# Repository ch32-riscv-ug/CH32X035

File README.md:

# CH32X035

<!-- This file is generated from ch32-riscv-ug/ch32-device-data (index/ + evidence/ + pipeline/build/build_readme.py). Edit there, not here. -->

[Choose a part](#product-comparison) &middot; [Documents](#documents) &middot; [Pin maps](#pin-maps--alternate-functions) &middot; [Pin viewer](https://ch32-riscv-ug.github.io/ch32-device-data/pins.html?chip=CH32X033) &middot; [Errata](#errata) &middot; [Examples](#evt-examples) &middot; [Address map](#address-map)

## Quick start

Programming and debug: **2-wire SDI** (WCH-Link, `Serial Debug Interface`).

### Debug / serial defaults

Where these land **without writing a remap register**. SWD is live at reset; the UART pads are not -- the pin must still be put into alternate-function mode. See `route` in evidence/README.ja.md.

| Series | SWDIO | SWCLK | UART TX | UART RX |
|---|---|---|---|---|
| CH32X033 | PC18 | PC19 | PA2 (USART2); PB0 (USART4) | PA3 (USART2); PB1 (USART4) |
| CH32X035 | PC18 | PC19 | PB10 (USART1); PA2 (USART2) | PB11 (USART1); PA3 (USART2) |

### Datasheets and reference manual

- CH32X035DS0.PDF (datasheet): [English](https://ch32-riscv-ug.github.io/CH32X035/datasheet_en/CH32X035DS0.PDF) · [中文](https://ch32-riscv-ug.github.io/CH32X035/datasheet_zh/CH32X035DS0.PDF)
- CH32X035RM.PDF (reference manual): [English](https://ch32-riscv-ug.github.io/CH32X035/datasheet_en/CH32X035RM.PDF) · [中文](https://ch32-riscv-ug.github.io/CH32X035/datasheet_zh/CH32X035RM.PDF)

## Series

| Series | Core | ISA | Flash | SRAM | Main clock | VDD | Packages | Products | Official |
|---|---|---|---|---|---|---|---|---|---|
| **CH32X033** | QingKe V4C | RV32IMAC | 62K | 20K | 48 MHz\* | 2.0-5.5V | TSSOP20 | 1 | [en](https://www.wch-ic.com/products/CH32X033.html) / [zh](https://www.wch.cn/products/CH32X033.html) |
| **CH32X035** | QingKe V4C | RV32IMAC | 62K | 20K | 48 MHz\* | 2.0-5.5V | LQFP48,LQFP64M,QFN12,QFN20,QFN28,QSOP28,TSSOP20 | 7 | [en](https://www.wch-ic.com/products/CH32X035.html) / [zh](https://www.wch.cn/products/CH32X035.html) |

\* the datasheet states no nominal system main frequency for this series, so the figure is the electrical maximum (HCLK) from the characteristics table -- a limit, not a rating.

## Product comparison

### CH32X035 product comparison

Only the 7 rows that differ between these 7 products; the other 10 are the same for all of them.

| | [CH32X035&#8203;C8T6](https://ch32-riscv-ug.github.io/ch32-device-data/pins.html?chip=CH32X035C8T6)&#8203;(LQFP48) | [CH32X035&#8203;D8U6](https://ch32-riscv-ug.github.io/ch32-device-data/pins.html?chip=CH32X035D8U6)&#8203;(QFN12) | [CH32X035&#8203;F7P6](https://ch32-riscv-ug.github.io/ch32-device-data/pins.html?chip=CH32X035F7P6)&#8203;(TSSOP20) | [CH32X035&#8203;F8U6](https://ch32-riscv-ug.github.io/ch32-device-data/pins.html?chip=CH32X035F8U6)&#8203;(QFN20) | [CH32X035&#8203;G8R6](https://ch32-riscv-ug.github.io/ch32-device-data/pins.html?chip=CH32X035G8R6)&#8203;(QSOP28) | [CH32X035&#8203;G8U6](https://ch32-riscv-ug.github.io/ch32-device-data/pins.html?chip=CH32X035G8U6)&#8203;(QFN28) | [CH32X035&#8203;R8T6](https://ch32-riscv-ug.github.io/ch32-device-data/pins.html?chip=CH32X035R8T6)&#8203;(LQFP64M) |
|---|---|---|---|---|---|---|---|
| **GPIO** | 46 | 11 | 18 | 19 | 26 | 27 | 60 |
| Serial port | 4 | 3 | 3 | 3 | 4 | 4 | 4 |
| PDUSB USB Host | √ | - | - | - | √ | √ | √ |
| ADC | 10+1 | 5+1 | 11+1 | 10+1 | 11+1 | 12+1 | 14+1 |
| OPA | 2 | 1 | 1 | 2 | 2 | 2 | 2 |
| CMP | 3 | - | 1 | - | 3 | 1 | 3 |
| Capacitive Touchkey | 10 | 5 | 11 | 10 | 11 | 12 | 14 |

<details><summary>All 17 rows</summary>

| | [CH32X035&#8203;C8T6](https://ch32-riscv-ug.github.io/ch32-device-data/pins.html?chip=CH32X035C8T6)&#8203;(LQFP48) | [CH32X035&#8203;D8U6](https://ch32-riscv-ug.github.io/ch32-device-data/pins.html?chip=CH32X035D8U6)&#8203;(QFN12) | [CH32X035&#8203;F7P6](https://ch32-riscv-ug.github.io/ch32-device-data/pins.html?chip=CH32X035F7P6)&#8203;(TSSOP20) | [CH32X035&#8203;F8U6](https://ch32-riscv-ug.github.io/ch32-device-data/pins.html?chip=CH32X035F8U6)&#8203;(QFN20) | [CH32X035&#8203;G8R6](https://ch32-riscv-ug.github.io/ch32-device-data/pins.html?chip=CH32X035G8R6)&#8203;(QSOP28) | [CH32X035&#8203;G8U6](https://ch32-riscv-ug.github.io/ch32-device-data/pins.html?chip=CH32X035G8U6)&#8203;(QFN28) | [CH32X035&#8203;R8T6](https://ch32-riscv-ug.github.io/ch32-device-data/pins.html?chip=CH32X035R8T6)&#8203;(LQFP64M) |
|---|---|---|---|---|---|---|---|
| **Flash** | 62K | 62K | 62K | 62K | 62K | 62K | 62K |
| **SRAM** | 20K | 20K | 20K | 20K | 20K | 20K | 20K |
| **GPIO** | 46 | 11 | 18 | 19 | 26 | 27 | 60 |
| **Temperature** | -40..85C | -40..85C | -40..85C | -40..85C | -40..85C | -40..85C | -40..85C |
| Advanced-control timer | 2 | 2 | 2 | 2 | 2 | 2 | 2 |
| General-purpose timer | 1 | 1 | 1 | 1 | 1 | 1 | 1 |
| Serial port | 4 | 3 | 3 | 3 | 4 | 4 | 4 |
| Watchdog | 2 | 2 | 2 | 2 | 2 | 2 | 2 |
| PDUSB USB Host | √ | - | - | - | √ | √ | √ |
| USB Device | √ | √ | √ | √ | √ | √ | √ |
| Type-C Source Sink DRP | √ | √ | √ | √ | √ | √ | √ |
| ADC | 10+1 | 5+1 | 11+1 | 10+1 | 11+1 | 12+1 | 14+1 |
| OPA | 2 | 1 | 1 | 2 | 2 | 2 | 2 |
| CMP | 3 | - | 1 | - | 3 | 1 | 3 |
| Capacitive Touchkey | 10 | 5 | 11 | 10 | 11 | 12 | 14 |
| SPI | √ | √ | √ | √ | √ | √ | √ |
| PIOC 1-wire interface | √ | √ | √ | √ | √ | √ | √ |

</details>

## Block diagrams

### CH32X033

<details><summary>Internal block diagram (datasheet)</summary>

</details>

### CH32X035

System block diagram from the [WCH product page](https://www.wch-ic.com/products/CH32X035.html).

<details><summary>Internal block diagram (datasheet)</summary>

</details>

## Documents

| Document | Kind | English | 中文 |
|---|---|---|---|
| CH32X035DS0.PDF | datasheet | [page](https://www.wch-ic.com/downloads/CH32X035DS0_PDF.html) [mirror](https://ch32-riscv-ug.github.io/CH32X035/datasheet_en/CH32X035DS0.PDF) v2.3 | [page](https://www.wch.cn/downloads/CH32X035DS0_PDF.html) [mirror](https://ch32-riscv-ug.github.io/CH32X035/datasheet_zh/CH32X035DS0.PDF) v2.3 |
| CH32X035RM.PDF | reference-manual | [page](https://www.wch-ic.com/downloads/CH32X035RM_PDF.html) [mirror](https://ch32-riscv-ug.github.io/CH32X035/datasheet_en/CH32X035RM.PDF) v1.9 | [page](https://www.wch.cn/downloads/CH32X035RM_PDF.html) [mirror](https://ch32-riscv-ug.github.io/CH32X035/datasheet_zh/CH32X035RM.PDF) v2.0 |
| CH32X035EVT.ZIP | evt | - | [page](https://www.wch.cn/downloads/CH32X035EVT_ZIP.html) [mirror](https://github.com/ch32-riscv-ug/CH32X035/tree/main/EVT) v2.31 |
| CHRISC8B.PDF | core-manual | [mirror](https://ch32-riscv-ug.github.io/CH32X035/EVT/EXAM/PIOC/Tool_Manual/Manual/CHRISC8B-EN.pdf) v2B | [mirror](https://ch32-riscv-ug.github.io/CH32X035/EVT/EXAM/PIOC/Tool_Manual/Manual/CHRISC8B.PDF) v2B |
| PIOC.PDF | core-manual | [mirror](https://ch32-riscv-ug.github.io/CH32X035/EVT/EXAM/PIOC/Tool_Manual/Manual/PIOC-EN.pdf) v1.0 | [mirror](https://ch32-riscv-ug.github.io/CH32X035/EVT/EXAM/PIOC/Tool_Manual/Manual/PIOC.PDF) v1.1 |

### Evaluation boards

- board-manual:en: [CH32X035 Evaluation Board Reference-EN.pdf](https://ch32-riscv-ug.github.io/CH32X035/EVT/PUB/CH32X035%20Evaluation%20Board%20Reference-EN.pdf)
- board-manual:zh: [CH32X035评估板说明书.pdf](https://ch32-riscv-ug.github.io/CH32X035/EVT/PUB/CH32X035%E8%AF%84%E4%BC%B0%E6%9D%BF%E8%AF%B4%E6%98%8E%E4%B9%A6.pdf)
- schematic-pdf: [CH32X035SCH.pdf](https://ch32-riscv-ug.github.io/CH32X035/EVT/PUB/CH32X035SCH.pdf)

7 board schematics under `EVT/PUB/SCHPCB/`: `CH32X033F8P-R0`, `CH32X035C8T-R0`, `CH32X035F7P-R0`, `CH32X035F8U-R0`, `CH32X035G8R-R0`, `CH32X035G8U-R0`, `CH32X035USBPD-CH211`

## Packages & pinout drawings

Pinout drawings are in the datasheet (chapter *Pinouts*); each link opens at the page that carries the drawing:

| Package | Products | Datasheet | Outline |
|---|---|---|---|
| TSSOP20 | CH32X033F8P6 | [en](https://ch32-riscv-ug.github.io/CH32X035/datasheet_en/CH32X035DS0.PDF#page=16) / [zh](https://ch32-riscv-ug.github.io/CH32X035/datasheet_zh/CH32X035DS0.PDF#page=15) | [drawing](https://raw.githubusercontent.com/ch32-riscv-ug/WCH-common/main/image/package_TSSOP20.png) |
| LQFP48 | CH32X035C8T6 | [en](https://ch32-riscv-ug.github.io/CH32X035/datasheet_en/CH32X035DS0.PDF#page=13) / [zh](https://ch32-riscv-ug.github.io/CH32X035/datasheet_zh/CH32X035DS0.PDF#page=12) | [drawing](https://raw.githubusercontent.com/ch32-riscv-ug/WCH-common/main/image/package_LQFP48.png) |
| QFN12 | CH32X035D8U6 | [en](https://ch32-riscv-ug.github.io/CH32X035/datasheet_en/CH32X035DS0.PDF#page=15) / [zh](https://ch32-riscv-ug.github.io/CH32X035/datasheet_zh/CH32X035DS0.PDF#page=14) | [drawing](https://raw.githubusercontent.com/ch32-riscv-ug/WCH-common/main/image/package_QFN12.png) |
| TSSOP20 | CH32X035F7P6 | [en](https://ch32-riscv-ug.github.io/CH32X035/datasheet_en/CH32X035DS0.PDF#page=13) / [zh](https://ch32-riscv-ug.github.io/CH32X035/datasheet_zh/CH32X035DS0.PDF#page=12) | [drawing](https://raw.githubusercontent.com/ch32-riscv-ug/WCH-common/main/image/package_TSSOP20.png) |
| QFN20 | CH32X035F8U6 | [en](https://ch32-riscv-ug.github.io/CH32X035/datasheet_en/CH32X035DS0.PDF#page=15) / [zh](https://ch32-riscv-ug.github.io/CH32X035/datasheet_zh/CH32X035DS0.PDF#page=14) | [drawing](https://raw.githubusercontent.com/ch32-riscv-ug/WCH-common/main/image/package_QFN20.png) |
| QSOP28 | CH32X035G8R6 | [en](https://ch32-riscv-ug.github.io/CH32X035/datasheet_en/CH32X035DS0.PDF#page=14) / [zh](https://ch32-riscv-ug.github.io/CH32X035/datasheet_zh/CH32X035DS0.PDF#page=13) | [drawing](https://raw.githubusercontent.com/ch32-riscv-ug/WCH-common/main/image/package_QSOP28.png) |
| QFN28 | CH32X035G8U6 | [en](https://ch32-riscv-ug.github.io/CH32X035/datasheet_en/CH32X035DS0.PDF#page=14) / [zh](https://ch32-riscv-ug.github.io/CH32X035/datasheet_zh/CH32X035DS0.PDF#page=13) | [drawing](https://raw.githubusercontent.com/ch32-riscv-ug/WCH-common/main/image/package_QFN28.png) |
| LQFP64M | CH32X035R8T6 | [en](https://ch32-riscv-ug.github.io/CH32X035/datasheet_en/CH32X035DS0.PDF#page=12) / [zh](https://ch32-riscv-ug.github.io/CH32X035/datasheet_zh/CH32X035DS0.PDF#page=11) | [drawing](https://raw.githubusercontent.com/ch32-riscv-ug/WCH-common/main/image/package_LQFP64M.png) |

## Pin maps & alternate functions

> [!NOTE]
> These are the **pin-table superset**: the datasheet prints one pad table for every product that shares a pinout, so a pad row does not mean this part has the peripheral. Use the product comparison table above for what a given part number contains.

### CH32X033 pin map

Pin functions (filterable): [ALL](https://ch32-riscv-ug.github.io/ch32-device-data/pins.html?chip=CH32X033) [ADC](https://ch32-riscv-ug.github.io/ch32-device-data/pins.html?chip=CH32X033&features=ADC) [I2C](https://ch32-riscv-ug.github.io/ch32-device-data/pins.html?chip=CH32X033&features=I2C) [SPI](https://ch32-riscv-ug.github.io/ch32-device-data/pins.html?chip=CH32X033&features=SPI) [SYS](https://ch32-riscv-ug.github.io/ch32-device-data/pins.html?chip=CH32X033&features=SYS) [TIM](https://ch32-riscv-ug.github.io/ch32-device-data/pins.html?chip=CH32X033&features=TIM) [UART](https://ch32-riscv-ug.github.io/ch32-device-data/pins.html?chip=CH32X033&features=UART) [USB](https://ch32-riscv-ug.github.io/ch32-device-data/pins.html?chip=CH32X033&features=USB)

<details><summary><b>CH32X033 pin map</b> (23 pads x 1 products)</summary>

| Pin name | Type | [CH32X033&#8203;F8P6](https://ch32-riscv-ug.github.io/ch32-device-data/pins.html?chip=CH32X033F8P6)&#8203;(TSSOP20) | Notes |
|---|---|---|---|
| PA0 | I/O/A | 14 |  |
| PA1 | I/O/A | 15 |  |
| PA2 | I/O/A | 16 | UART TX (USART2) |
| PA3 | I/O/A | 17 | UART RX (USART2) |
| PA4 | I/O/A | 19 |  |
| PA5 | I/O/A | 20 |  |
| PA6 | I/O/A | 1 |  |
| PA7 | I/O/A | 2 |  |
| PA9 | I/O | 10 |  |
| PA10 | I/O | 12 |  |
| PA11 | I/O/A | 11 |  |
| PB0 | I/O/A | 2 | UART TX (USART4) |
| PB1 | I/O/A | 3 | UART RX (USART4) |
| PB7 | I/O/A | 4 |  |
| PC3 | I/O/A | 13 |  |
| PC10 | I/O | 6 |  |
| PC11 | I/O | 5 |  |
| PC16 | I/O/A | 5 |  |
| PC17 | I/O/A | 6 |  |
| PC18 | I/O | 8 | SWDIO |
| PC19 | I/O/A | 18 | SWCLK |
| GND | P | 7 |  |
| VDD | P | 9 |  |

</details>

<details><summary><b>CH32X033 alternate functions</b></summary>

| Pad | default | remap-1 | remap-2 | remap-3 | remap-4 | remap-5 | remap-6 |
|---|---|---|---|---|---|---|---|
| PA0 | A0, C1P1, CTS2, T2C1 | - | T2C1 | - | - | - | - |
| PA1 | A1, C1O, O1N2, O2N2, RTS2, T2C2 | CTS2 | T2C2 | - | - | - | - |
| PA2 | A2, C3N0, O2O1, T2C3, TX2 | RTS2, T2C3 | - | - | - | T2ET | T2ET |
| PA3 | A3, O1O0, RX2, T2C4 | T2C4 | CTS3 | T3C1 | - | - | - |
| PA4 | A4, CK2, CS, O2O0 | - | RTS3 | T3C2 | - | - | - |
| PA5 | A5, O2N0, SCK | TX4 | - | - | CTS4 | - | - |
| PA6 | A6, MISO, O1N0, T3C1 | CK4, T1BK | - | - | RTS4 | - | - |
| PA7 | A7, MOSI, O2P0, T3C2 | CTS4, T1C1N | - | TX1 | - | - | - |
| PA9 | - | MOSI, RX4, T2BK | CTS1, MISO | T2BK | - | - | - |
| PA10 | SCL | TX1 | MOSI | RX4 | - | - | - |
| PA11 | C2P1, SDA | RX1 | SCK | - | - | - | - |
| PB0 | A8, O1P0, TX4 | T1C2N | - | - | - | - | - |
| PB1 | A9, O2N1, RX4 | T1C3N | - | - | - | - | - |
| PB7 | O2P2, RST, RTS3, T1C2N | RTS3 | T1C2N | - | - | - | - |
| PC3 | A13, C1N0, C2N1, C3N1 | - | T2C1N | RTS2, T1C4 | RTS2, T2C3N | - | - |
| PC16 | CTS1, T1C4, UDM | CTS1, T1C4 | SCL, TX4 | - | SDA | RX4 | - |
| PC17 | RTS1, T1ET, UDP | RTS1, T1ET | RX4, SDA | - | SCL | TX4 | - |
| PC18 | DIO, PIOC_IO0 | TX3 | T1ET, T3C2 | SDA, T1ET | - | SCL, T2C1N | - |
| PC19 | C1P0, DCK, PIOC_IO1 | RX3 | T3C1 | SCL | RX4 | SDA, T2C1 | T2C1 |

</details>

### CH32X035 pin map

Pin functions (filterable): [ALL](https://ch32-riscv-ug.github.io/ch32-device-data/pins.html?chip=CH32X035) [ADC](https://ch32-riscv-ug.github.io/ch32-device-data/pins.html?chip=CH32X035&features=ADC) [I2C](https://ch32-riscv-ug.github.io/ch32-device-data/pins.html?chip=CH32X035&features=I2C) [SPI](https://ch32-riscv-ug.github.io/ch32-device-data/pins.html?chip=CH32X035&features=SPI) [SYS](https://ch32-riscv-ug.github.io/ch32-device-data/pins.html?chip=CH32X035&features=SYS) [TIM](https://ch32-riscv-ug.github.io/ch32-device-data/pins.html?chip=CH32X035&features=TIM) [UART](https://ch32-riscv-ug.github.io/ch32-device-data/pins.html?chip=CH32X035&features=UART) [USB](https://ch32-riscv-ug.github.io/ch32-device-data/pins.html?chip=CH32X035&features=USB)

<details><summary><b>CH32X035 pin map</b> (64 pads x 7 products)</summary>

| Pin name | Type | [CH32X035&#8203;C8T6](https://ch32-riscv-ug.github.io/ch32-device-data/pins.html?chip=CH32X035C8T6)&#8203;(LQFP48) | [CH32X035&#8203;D8U6](https://ch32-riscv-ug.github.io/ch32-device-data/pins.html?chip=CH32X035D8U6)&#8203;(QFN12) | [CH32X035&#8203;F7P6](https://ch32-riscv-ug.github.io/ch32-device-data/pins.html?chip=CH32X035F7P6)&#8203;(TSSOP20) | [CH32X035&#8203;F8U6](https://ch32-riscv-ug.github.io/ch32-device-data/pins.html?chip=CH32X035F8U6)&#8203;(QFN20) | [CH32X035&#8203;G8R6](https://ch32-riscv-ug.github.io/ch32-device-data/pins.html?chip=CH32X035G8R6)&#8203;(QSOP28) | [CH32X035&#8203;G8U6](https://ch32-riscv-ug.github.io/ch32-device-data/pins.html?chip=CH32X035G8U6)&#8203;(QFN28) | [CH32X035&#8203;R8T6](https://ch32-riscv-ug.github.io/ch32-device-data/pins.html?chip=CH32X035R8T6)&#8203;(LQFP64M) | Notes |
|---|---|---|---|---|---|---|---|---|---|
| PA0 | I/O/A | 10 | - | 6 | 2 | 9 | 5 | 14 |  |
| PA1 | I/O/A | 11 | - | 7 | 3 | 10 | 6 | 15 |  |
| PA2 | I/O/A | 12 | 2 | 8 | 4 | 11 | 7 | 16 | UART TX (USART2) |
| PA3 | I/O/A | 13 | 3 | 9 | 5 | 12 | 8 | 17 | UART RX (USART2) |
| PA4 | I/O/A | 14 | - | 10 | 6 | 15 | 9 | 20 |  |
| PA5 | I/O/A | 15 | 4 | 11 | 7 | 16 | 10 | 21 |  |
| PA6 | I/O/A | 16 | 5 | 12 | 8 | 13 | 11 | 22 |  |
| PA7 | I/O/A | 17 | 6 | 13 | 9 | 17 | 12 | 23 |  |
| PA8 | I/O | 40 | - | - | - | - | - | 56 |  |
| PA9 | I/O | 41 | - | - | - | - | - | 57 |  |
| PA10 | I/O | 42 | - | - | - | - | - | 58 |  |
| PA11 | I/O/A | 43 | - | - | - | - | - | 59 |  |
| PA12 | I/O/A | 44 | - | - | - | 4 | - | 60 |  |
| PA13 | I/O/A | 45 | - | - | - | 5 | - | 61 |  |
| PA14 | I/O/A | 46 | - | - | - | - | - | 62 |  |
| PA15 | I/O | 1 | - | - | - | - | - | 1 |  |
| PA16 | I/O | 2 | - | - | - | - | - | 2 |  |
| PA17 | I/O | 3 | - | - | - | - | - | 3 |  |
| PA18 | I/O | 4 | - | - | - | - | - | 4 |  |
| PA19 | I/O | 5 | - | - | - | - | - | 5 |  |
| PA20 | I/O | 6 | - | - | - | - | - | 6 |  |
| PA21 | I/O | 7 | - | - | - | - | - | 7 |  |
| PA22 | I/O/A | 8 | - | - | - | - | - | 12 |  |
| PA23 | I/O/A | 9 | - | - | - | - | - | 13 |  |
| PB0 | I/O/A | 20 | - | - | 10 | 14 | 13 | 26 | UART TX (USART4) |
| PB1 | I/O/A | 21 | - | 14 | 11 | 20 | 16 | 27 | UART RX (USART4) |
| PB2 | I/O/A | 22 | - | - | - | - | - | 28 |  |
| PB3 | I/O/A | 23 | - | - | 12 | 18 | 14 | 29 | UART TX (USART3) |
| PB4 | I/O/A | 24 | - | - | - | 19 | 15 | 30 | UART RX (USART3) |
| PB5 | I/O/A | 25 | - | - | - | 20 | 16 | 33 |  |
| PB6 | I/O/A | 26 | - | - | - | 21 | 17 | 34 |  |
| PB7 | I/O/A | 27 | - | - | - | 22 | 18 | 35 |  |
| PB8 | I/O/A | 28 | - | - | - | 23 | 19 | 36 |  |
| PB9 | I/O | 29 | - | - | - | 24 | 20 | 41 |  |
| PB10 | I/O | 30 | - | - | - | 25 | 21 | 42 | UART TX (USART1) |
| PB11 | I/O | 31 | - | - | 13 | 26 | 22 | 43 | UART RX (USART1) |
| PB12 | I/O | 35 | - | 1 | 15 | 27 | 23 | 47 |  |
| PB13 | I/O | 36 | - | - | - | - | - | 48 |  |
| PB14 | I/O | - | - | - | - | - | - | 50 |  |
| PB15 | I/O | - | - | - | - | - | - | 53 |  |
| PB16 | I/O | - | - | - | - | - | - | 37 |  |
| PB17 | I/O | - | - | - | - | - | - | 38 |  |
| PB18 | I/O | - | - | - | - | - | - | 39 |  |
| PB19 | I/O | - | - | - | - | - | - | 40 |  |
| PB20 | I/O | - | - | - | - | - | - | 51 |  |
| PB21 | I/O | - | - | - | - | - | - | 52 |  |
| PC0 | I/O/A | - | - | - | - | - | 3 | 8 |  |
| PC1 | I/O/A | - | - | 5 | - | - | - | 9 |  |
| PC2 | I/O/A | - | - | - | - | - | - | 10 |  |
| PC3 | I/O/A | - | - | 4 | - | 8 | 4 | 11 |  |
| PC4 | I/O | - | - | - | - | - | - | 18 |  |
| PC5 | I/O | - | - | - | - | - | - | 19 |  |
| PC6 | I/O | 18 | - | - | - | - | - | 24 |  |
| PC7 | I/O | 19 | 6 | - | - | - | - | 25 |  |
| PC10 | I/O | 33 | - | 18 | - | 3 | 27 | 45 |  |
| PC11 | I/O | 32 | - | 17 | - | 2 | 26 | 44 |  |
| PC14 | I/O/A | 38 | 11 | 2 | 19 | 4 | 28 | 54 |  |
| PC15 | I/O/A | 39 | 12 | 3 | 20 | 5 | 1 | 55 |  |
| PC16 | I/O/A | 32 | 7 | 17 | 17 | 2 | 26 | 44 |  |
| PC17 | I/O/A | 33 | 8 | 18 | 18 | 3 | 27 | 45 |  |
| PC18 | I/O | 34 | 9 | 19 | 14 | 28 | 25 | 46 | SWDIO |
| PC19 | I/O/A | 37 | 10 | 20 | 16 | 1 | 24 | 49 | SWCLK |
| GND | P | 47 | EP | 15 | EP | 7 | EP | 31/63 |  |
| VDD | P | 48 | 1 | 16 | 1 | 6 | 2 | 32/64 |  |

</details>

<details><summary><b>CH32X035 alternate functions</b></summary>

| Pad | default | remap-1 | remap-2 | remap-3 | remap-4 | remap-5 | remap-6 |
|---|---|---|---|---|---|---|---|
| PA0 | A0, C1P1, CTS2, T2C1 | - | T2C1 | - | - | - | - |
| PA1 | A1, C1O, O1N2, O2N2, RTS2, T2C2 | CTS2 | T2C2 | - | - | - | - |
| PA2 | A2, C3N0, O2O1, T2C3, TX2 | RTS2, T2C3 | - | - | - | T2ET | T2ET |
| PA3 | A3, O1O0, RX2, T2C4 | T2C4 | CTS3 | T3C1 | - | - | - |
| PA4 | A4, CK2, CS, O2O0 | - | RTS3 | T3C2 | - | - | - |
| PA5 | A5, O2N0, SCK | TX4 | - | - | CTS4 | - | - |
| PA6 | A6, MISO, O1N0, T3C1 | CK4, T1BK | - | - | RTS4 | - | - |
| PA7 | A7, MOSI, O2P0, T3C2 | CTS4, T1C1N | - | TX1 | - | - | - |
| PA8 | RTS4 | MISO | RTS1, RTS4 | - | CK4 | RTS4 | - |
| PA9 | - | MOSI, RX4, T2BK | CTS1, MISO | T2BK | - | - | - |
| PA10 | SCL | TX1 | MOSI | RX4 | - | - | - |
| PA11 | C2P1, SDA | RX1 | SCK | - | - | - | - |
| PA12 | C2P0 | T2C1N | CS | T2C1N | - | T2C2 | - |
| PA13 | C3P0 | SCL, T2C2N | - | CTS1, RTS4, T2C2N | - | T2C3 | - |
| PA14 | C3P1 | SDA, T2C3N | - | CTS4, RTS1, T2C3N | - | - | - |
| PA15 | - | - | TX2 | - | TX2 | - | - |
| PA16 | - | - | RX2 | - | RX2 | - | - |
| PA17 | - | - | CTS2 | - | CTS2 | - | - |
| PA18 | - | T2ET | TX3 | T2ET | - | - | - |
| PA19 | T2ET | RX2 | T2ET | - | - | - | - |
| PA20 | T2BK | TX2 | T2BK | - | - | - | - |
| PA21 | RST, T2C1N | - | RTS2 | - | - | - | - |
| PA22 | C2N0, T2C2N | - | CK2, T2C2N | - | CK2 | - | - |
| PA23 | C1N1, T2C3N | CK2 | T2C3N | - | - | - | - |
| PB0 | A8, O1P0, TX4 | T1C2N | - | - | - | - | - |
| PB1 | A9, O2N1, RX4 | T1C3N | - | - | - | - | - |
| PB2 | C2O, CK4 | - | CK4 | RX1 | - | CK4 | - |
| PB3 | C3O, O2P1, TX3 | - | T2C3 | T2C3 | - | T2C3N | T2C3N |
| PB4 | O1P2, RX3 | T3C1 | T2C4 | T2C4 | - | T2BK | T2BK |
| PB5 | CK3, O1O1, T1BK | CK3, T3C2 | CK1, T1BK | - | - | - | - |
| PB6 | CTS3, O1N1, T1C1N | CTS3 | T1C1N | - | - | - | - |
| PB7 | O2P2, RTS3, T1C2N | RTS3 | T1C2N | - | - | - | - |
| PB8 | O1P1, T1C3N | - | CK3, T1C3N | CK4 | - | - | - |
| PB9 | CK1, MCO, T1C1 | CK1, T1C1 | T1C1 | TX4 | - | - | - |
| PB10 | T1C2, TX1 | T1C2 | T1C2, TX1 | - | - | - | - |
| PB11 | RX1, T1C3 | T1C3 | RX1, T1C3 | - | - | - | T2C1N |
| PB12 | - | - | T1C4 | CK1 | - | T2C2N | T2C2N |
| PB13 | - | - | - | - | TX4 | - | - |
| PB14 | - | - | RX3 | - | - | - | - |
| PB15 | CTS4 | SCK, T2C2 | CTS4 | T2C2 | - | CTS4 | - |
| PB16 | - | - | - | TX3 | T2C1 | - | - |
| PB17 | - | - | - | RX3 | T2C2 | - | - |
| PB18 | - | - | - | CTS3 | T2C3 | - | - |
| PB19 | - | - | - | RTS3 | T2C4 | - | - |
| PB20 | - | - | - | CK2 | - | - | - |
| PB21 | - | CS, RTS4, T2C1 | - | T2C1 | - | - | - |
| PC0 | A10 | - | - | T1C1, TX2 | T2BK | T2C4 | T2C4 |
| PC1 | A11 | - | - | RX2, T1C2 | T2C1N | - | - |
| PC2 | A12 | - | - | CTS2, T1C3 | T2C2N | - | - |
| PC3 | A13, C1N0, C2N1, C3N1, RST | - | T2C1N | RTS2, T1C4 | RTS2, T2C3N | - | - |
| PC4 | - | - | - | CS, T1BK | T2ET | - | - |
| PC5 | - | - | - | SCK, T1C1N | - | - | - |
| PC6 | - | - | - | MISO, T1C2N | - | - | - |
| PC7 | - | PIOC_IO0 | - | MOSI, T1C3N | - | - | - |
| PC14 | CC1 | - | - | - | T1C3 | - | T2C2 |
| PC15 | CC2 | - | - | - | T1ET | - | T2C3 |
| PC16 | CTS1, T1C4, UDM | CTS1, T1C4 | SCL, TX4 | - | SDA | RX4 | - |
| PC17 | RTS1, T1ET, UDP | RTS1, T1ET | RX4, SDA | - | SCL | TX4 | - |
| PC18 | DIO, PIOC_IO0 | TX3 | T1ET, T3C2 | SDA, T1ET | - | SCL, T2C1N | - |
| PC19 | C1P0, DCK, PIOC_IO1 | RX3 | T3C1 | SCL | RX4 | SDA, T2C1 | T2C1 |

</details>

<details><summary><b>Remap selectors (AFIO)</b></summary>

| Series | Field | Register | Bits | Values | Reset |
|---|---|---|---|---|---|
| CH32X033 | I2C1_REMAP | PCFR1 | PCFR1:2;PCFR1:3;PCFR1:4 | 0;1;2;3;4;5;6;7 | 0 |
| CH32X033 | PIOC_REMAP | PCFR1 | PCFR1:23 | 0;1 | 0 |
| CH32X033 | SPI1_REMAP | PCFR1 | PCFR1:0;PCFR1:1 | 0;1;2;3 | 0 |
| CH32X033 | TIM1_REMAP | PCFR1 | PCFR1:15;PCFR1:16;PCFR1:17 | 0;1;2;3;4 | 0 |
| CH32X033 | TIM2_REMAP | PCFR1 | PCFR1:18;PCFR1:19;PCFR1:20 | 0;1;2;3;4;5;6;7 | 0 |
| CH32X033 | TIM3_REMAP | PCFR1 | PCFR1:21;PCFR1:22 | 0;1;2;3 | 0 |
| CH32X033 | USART1_REMAP | PCFR1 | PCFR1:5;PCFR1:6 | 0;1;2;3 | 0 |
| CH32X033 | USART2_REMAP | PCFR1 | PCFR1:7;PCFR1:8;PCFR1:9 | 0;1;2;3;4;5;6;7 | 0 |
| CH32X033 | USART3_REMAP | PCFR1 | PCFR1:10;PCFR1:11 | 0;1;2;3 | 0 |
| CH32X033 | USART4_REMAP | PCFR1 | PCFR1:12;PCFR1:13;PCFR1:14 | 0;1;2;3;4;5;6;7 | 0 |
| CH32X035 | I2C1_REMAP | PCFR1 | PCFR1:2;PCFR1:3;PCFR1:4 | 0;1;2;3;4;5;6;7 | 0 |
| CH32X035 | PIOC_REMAP | PCFR1 | PCFR1:23 | 0;1 | 0 |
| CH32X035 | SPI1_REMAP | PCFR1 | PCFR1:0;PCFR1:1 | 0;1;2;3 | 0 |
| CH32X035 | TIM1_REMAP | PCFR1 | PCFR1:15;PCFR1:16;PCFR1:17 | 0;1;2;3;4 | 0 |
| CH32X035 | TIM2_REMAP | PCFR1 | PCFR1:18;PCFR1:19;PCFR1:20 | 0;1;2;3;4;5;6;7 | 0 |
| CH32X035 | TIM3_REMAP | PCFR1 | PCFR1:21;PCFR1:22 | 0;1;2;3 | 0 |
| CH32X035 | USART1_REMAP | PCFR1 | PCFR1:5;PCFR1:6 | 0;1;2;3 | 0 |
| CH32X035 | USART2_REMAP | PCFR1 | PCFR1:7;PCFR1:8;PCFR1:9 | 0;1;2;3;4;5;6;7 | 0 |
| CH32X035 | USART3_REMAP | PCFR1 | PCFR1:10;PCFR1:11 | 0;1;2;3 | 0 |
| CH32X035 | USART4_REMAP | PCFR1 | PCFR1:12;PCFR1:13;PCFR1:14 | 0;1;2;3;4;5;6;7 | 0 |

</details>

## Errata

- Only UNIID1 and UNIID2 (the low 64 bits) of the unique ID differ between chips; UNIID3 is not unique although the reference manual describes a 96-bit unique identifier. UNIID3 reads 0xFFFFFFFF on the measured V003, V006, X035 and L103 chips, and the same 0xE339E339 on a V203 and a V307. Use UNIID1|UNIID2 as the chip's unique value. *(applies: CH32L103, CH32V003, CH32V006, CH32V203, CH32V307, CH32X035; )*
- ADC channels 3, 7, 11 and 15, and the I2C function, are not available. *(applies: CH32X033, CH32X035; 5th-to-last digit of lot number = 0)*
- On these lots an unavailable ADC channel does not read zero or fail: IN3 and IN7 return the value of the channel before them (IN2, IN6), so a wrong reading looks plausible. IN15 (VREFINT) also reads wrong. Do not sample these channels. *(applies: CH32X033, CH32X035; 5th-to-last digit of lot number = 0)*
- The X0 GPIO block has no general-purpose open-drain output: CNF=01 in output mode drives the pad high like push-pull (ch32-data gpio_x0 describes CNF=01 as "Floating input, no Open Drain output"). Only the AF open-drain mode (CNF=11) releases the pad, and then the peripheral owns it. Open-drain GPIO must be emulated as floating input / push-pull low. *(applies: CH32X033, CH32X035; )*
- The PC10/PC17 and PC11/PC16 pin pairs are internally bonded together; both IOs of a pair must not be configured as outputs at the same time. *(applies: CH32X033, CH32X035; except CH32X035F8U6 and CH32X035D8U6)*
- PC16 (UDM) and PC17 (UDP) belong to the USB PHY. While AFIO_CTLR.USB_PHY_V33 (bit 6, part of the reset value 0x45) is set, a GPIO or AF open-drain output on either pad drives high instead of releasing, so another device cannot pull the line low (an I2C target can never ACK). Clear the bit before using the pads as open-drain outputs. *(applies: CH32X033, CH32X035; )*

## EVT examples

109 routines in [EVT/EXAM](https://github.com/ch32-riscv-ug/CH32X035/tree/main/EVT/EXAM):

[ADC](https://github.com/ch32-riscv-ug/CH32X035/tree/main/EVT/EXAM/ADC) 5 · [APPLICATION](https://github.com/ch32-riscv-ug/CH32X035/tree/main/EVT/EXAM/APPLICATION) 1 · [DMA](https://github.com/ch32-riscv-ug/CH32X035/tree/main/EVT/EXAM/DMA) 2 · [EXTI](https://github.com/ch32-riscv-ug/CH32X035/tree/main/EVT/EXAM/EXTI) 1 · [FLASH](https://github.com/ch32-riscv-ug/CH32X035/tree/main/EVT/EXAM/FLASH) 2 · [FreeRTOS](https://github.com/ch32-riscv-ug/CH32X035/tree/main/EVT/EXAM/FreeRTOS) 1 · [GPIO](https://github.com/ch32-riscv-ug/CH32X035/tree/main/EVT/EXAM/GPIO) 1 · [HarmonyOS](https://github.com/ch32-riscv-ug/CH32X035/tree/main/EVT/EXAM/HarmonyOS) 1 · [I2C](https://github.com/ch32-riscv-ug/CH32X035/tree/main/EVT/EXAM/I2C) 6 · [IAP](https://github.com/ch32-riscv-ug/CH32X035/tree/main/EVT/EXAM/IAP) 1 · [INT](https://github.com/ch32-riscv-ug/CH32X035/tree/main/EVT/EXAM/INT) 1 · [IWDG](https://github.com/ch32-riscv-ug/CH32X035/tree/main/EVT/EXAM/IWDG) 1 · [OPA](https://github.com/ch32-riscv-ug/CH32X035/tree/main/EVT/EXAM/OPA) 8 · [PIOC](https://github.com/ch32-riscv-ug/CH32X035/tree/main/EVT/EXAM/PIOC) 18 · [PMP](https://github.com/ch32-riscv-ug/CH32X035/tree/main/EVT/EXAM/PMP) 1 · [PWR](https://github.com/ch32-riscv-ug/CH32X035/tree/main/EVT/EXAM/PWR) 5 · [RCC](https://github.com/ch32-riscv-ug/CH32X035/tree/main/EVT/EXAM/RCC) 2 · [RT-Thread](https://github.com/ch32-riscv-ug/CH32X035/tree/main/EVT/EXAM/RT-Thread) 2 · [RunInRam](https://github.com/ch32-riscv-ug/CH32X035/tree/main/EVT/EXAM/RunInRam) 1 · [SDI_Printf](https://github.com/ch32-riscv-ug/CH32X035/tree/main/EVT/EXAM/SDI_Printf) 1 · [SPI](https://github.com/ch32-riscv-ug/CH32X035/tree/main/EVT/EXAM/SPI) 6 · [TIM](https://github.com/ch32-riscv-ug/CH32X035/tree/main/EVT/EXAM/TIM) 13 · [TOUCHKEY](https://github.com/ch32-riscv-ug/CH32X035/tree/main/EVT/EXAM/TOUCHKEY) 1 · [TencentOS](https://github.com/ch32-riscv-ug/CH32X035/tree/main/EVT/EXAM/TencentOS) 1 · [USART](https://github.com/ch32-riscv-ug/CH32X035/tree/main/EVT/EXAM/USART) 10 · [USB](https://github.com/ch32-riscv-ug/CH32X035/tree/main/EVT/EXAM/USB) 13 · [USBPD](https://github.com/ch32-riscv-ug/CH32X035/tree/main/EVT/EXAM/USBPD) 3 · [WWDG](https://github.com/ch32-riscv-ug/CH32X035/tree/main/EVT/EXAM/WWDG) 1

## Reference

### Address map

| Region | Base | Kind |
|---|---|---|
| APB1PERIPH | `0x40000000` | bus |
| PERIPH | `0x40000000` | bus |
| APB2PERIPH | `0x40010000` | bus |
| AHBPERIPH | `0x40020000` | bus |
| FLASH | `0x00000000` | link-origin |
| RAM | `0x20000000` | link-origin |
| FLASH | `0x08000000` | memory |
| OB | `0x1ffff800` | memory |
| SRAM | `0x20000000` | memory |

`link-origin` is what the EVT linker scripts use; the `memory` row for FLASH is the address the device header states. Both windows are real -- CH32V307 answers at `0x08000000` and at `0x00000000`.

Peripheral base addresses are in [memory_map.csv](https://github.com/ch32-riscv-ug/ch32-device-data/blob/main/index/memory_map.csv); interrupt numbers in [interrupts.csv](https://github.com/ch32-riscv-ug/ch32-device-data/blob/main/index/interrupts.csv).

---
Data: [ch32-device-data](https://github.com/ch32-riscv-ug/ch32-device-data) (evidence/ and index/ -- each value carries its evidence and confidence there).

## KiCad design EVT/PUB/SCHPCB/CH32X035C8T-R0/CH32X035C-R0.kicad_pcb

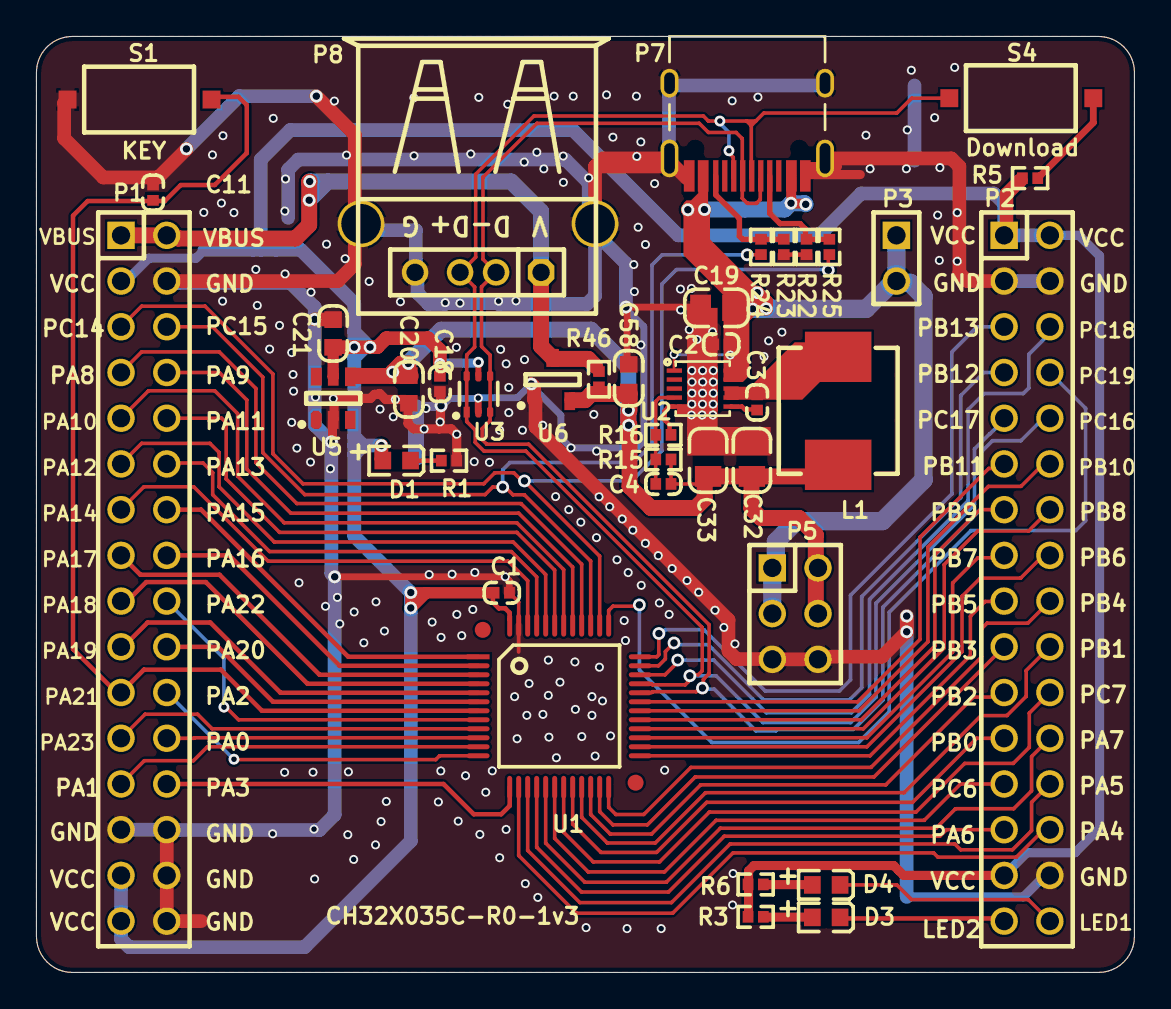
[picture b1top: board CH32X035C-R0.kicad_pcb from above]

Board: 2 copper layers, 61.0 x 52.0 mm, 40 parts (0 on the bottom side), 62 nets.

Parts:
C1, C11, C18: 0.1uF; 0402_C
C2: NC(0.1uF); 0402_C
C3: NC(100nF); 0402_C
C4: NC(68pF); 0402_C
C19: NC(22uF/35V); 0805_C
C20, C21, C58: 10uF; 0603_C
C32, C33: NC(22uF); 0805_C
D1: RED; 0603+
D3: LED2; 0603+
D4: LED1; 0603+
L1: NC(4.7uH); IND-SMD_L7.0-W6.6
P1, P2: Header 16X2; IDC32-2.54mm
P3: HEADER 2; SIP2-2.54mm
P5: HEADER 3x2; IDC6-2.54mm
P7: TYPE-C; TYPE-C-Receptacle-2.0
P8: USB_A; USBAF
R1, R3, R6: 1K; 0402
R5: 4.7K; 0402
R15: NC(15K); 0402
R16: NC(4.7K); 0402
R22, R23: 5.1K; 0402
R24, R25: 0Ω; 0402
R46: NC(0Ω); 0402
S1: KEY; SMD_6.1x3.65x2.5mm-KEY
S4: Download; SMD_6.1x3.65x2.5mm-KEY
U1: CH32X035C8T6; LQFP48
U2: NC(CH2024Q); DFN10_3X3
U3: CH412K; SOT-363
U5: CH2003K; SOT-23-6
U6: CH213; SOT-23-3

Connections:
3V3: C1.2, C18.2, C21.2, D1.1, P1.3, P1.29, P1.31, P2.1, P2.2, P2.29, R3.1, R5.1, R6.1, U1.48, U3.5, U5.5
+5V: C4.1, C20.2, C32.2, C33.2, C58.1, L1.2, P5.2, P5.4, R15.2, R46.1, U5.4, U6.2
CC1: P1.5, R25.2, U1.38
CC2: P1.6, R24.1, U1.39
FB: C4.2, R15.1, R16.2, U2.4
GND: C1.1, C2.1, C11.1, C18.1, C19.1, C20.1, C21.1, C32.1, C33.1, C58.2, P1.4, P1.27, P1.28, P1.30, P1.32, P2.3, P2.4, P2.30, P5.5, P5.6, P7.0, P7.A1, P7.B1, P8.0, P8.4, R1.2, R16.1, R22.2, R23.2, S1.2, U1.47, U2.0, U2.5, U3.2, U5.2, U6.1
LED1: D4.2, P2.32
LED2: D3.2, P2.31
NetC3_1: C3.1, U2.6
NetC3_2: C3.2, L1.1, U2.7, U2.8
NetD1_2: D1.2, R1.1
NetD3_1: D3.1, R3.2
NetD4_1: D4.1, R6.2
NetP7_A5: P7.A5, R22.1, R25.1
NetP7_B5: P7.B5, R23.1, R24.2
NetR5_2: R5.2, S4.1
PA0: P1.24, U1.10
PA1: P1.25, U1.11
PA2: P1.22, U1.12
PA3: P1.26, U1.13
PA4: P2.28, U1.14
PA5: P2.26, U1.15
PA6: P2.27, U1.16
PA7: P2.24, U1.17
PA8: P1.7, U1.40
PA9: P1.8, U1.41
PA10: P1.9, U1.42
PA11: P1.10, U1.43
PA12: P1.11, U1.44
PA13: P1.12, U1.45
PA14: P1.13, U1.46
PA15: P1.14, U1.1
PA16: P1.16, U1.2
PA17: P1.15, U1.3
PA18: P1.17, U1.4
PA19: P1.19, U1.5
PA20: P1.20, U1.6
PA21: C11.2, P1.21, S1.1, U1.7
PA22: P1.18, U1.8
PA23: P1.23, U1.9
PB0: P2.23, U1.20
PB1: P2.20, U1.21
PB2: P2.21, U1.22
PB3: P2.19, U1.23
PB4: P2.18, U1.24
PB5: P2.17, U1.25
PB6: P2.16, U1.26
PB7: P2.15, U1.27
PB8: P2.14, U1.28
PB9: P2.13, U1.29
PB10: P2.12, U1.30
PB11: P2.11, U1.31
PB12: P2.7, U1.35
PB13: P2.5, U1.36
PC6: P2.25, U1.18
PC7: P2.22, U1.19
PC16: P2.10, P7.A7, P7.B7, P8.2, U1.32, U3.3, U3.4
PC17: P2.9, P7.A6, P7.B6, P8.3, S4.2, U1.33, U3.1, U3.6
PC18: P2.6, U1.34
PC19: P2.8, U1.37
VBUS: P1.1, P1.2, P8.1, R46.2, U6.3
VBUS1: C2.2, C19.2, P3.1, P3.2, P5.1, P5.3, P7.A4, P7.B4, U2.1, U2.9, U2.10

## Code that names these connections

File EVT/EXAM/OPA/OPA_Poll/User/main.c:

/********************************** (C) COPYRIGHT *******************************
 * File Name          : main.c
 * Author             : WCH
 * Version            : V1.0.2
 * Date               : 2026/10/16
 * Description        : Main program body.
 *********************************************************************************
 * Copyright (c) 2021 Nanjing Qinheng Microelectronics Co., Ltd.
 * Attention: This software (modified or not) and binary are used for 
 * microcontroller manufactured by Nanjing Qinheng Microelectronics.
 *******************************************************************************/

/*
 *@Note
 *OPA POLL routine:
 *OPA2_CHP --PA7  PB3  PB7
 *OPA2_CHN1--PA5
 *OPA2_OUT--PA4
 *
 *The number of positive terminals polling is 3, and the polling interval is 81uS.
 *When doing comparison follow-up, input different voltage values , the three positive
 *directions, and the output terminal voltage will output the positive terminal voltage according to the polling interval.
 *when OPA POLL end enter IRQ.
 *
 */
#include "debug.h"
vu8  IntResponse=0 ;
/*********************************************************************
 * @fn      OPA2_Init
 *
 * @brief   Initializes OPA2.
 *
 * @return  none
 */
void OPA2_Init( void )
{
    GPIO_InitTypeDef GPIO_InitStructure = {0};
    OPA_InitTypeDef  OPA_InitStructure = {0};
    NVIC_InitTypeDef NVIC_InitStructure = {0};

    RCC_APB2PeriphClockCmd( RCC_APB2Periph_GPIOA, ENABLE );
    GPIO_InitStructure.GPIO_Pin = GPIO_Pin_7|GPIO_Pin_5|GPIO_Pin_4;
    GPIO_InitStructure.GPIO_Mode = GPIO_Mode_AIN;
    GPIO_Init( GPIOA, &GPIO_InitStructure );

    NVIC_InitStructure.NVIC_IRQChannel = OPA_IRQn;
    NVIC_InitStructure.NVIC_IRQChannelPreemptionPriority = 1;
    NVIC_InitStructure.NVIC_IRQChannelSubPriority = 2;
    NVIC_InitStructure.NVIC_IRQChannelCmd = ENABLE;
    NVIC_Init(&NVIC_InitStructure);

    OPA_InitStructure.OPA_NUM=OPA2;
    OPA_InitStructure.NSEL = CHN0;
    OPA_InitStructure.PSEL = CHP_OFF;
    OPA_InitStructure.POLL_NUM=CHP_POLL_NUM_3;
    OPA_InitStructure.PSEL_POLL=CHP_OPA1_OFF_OPA2_ON;
    OPA_InitStructure.OPA_POLL_Interval=0x50;
    OPA_InitStructure.Mode=OUT_IO_OUT0;
    OPA_InitStructure.CNT_IE=CNT_IE_ON;

    OPA_Init( &OPA_InitStructure );
    OPA_Cmd(OPA2, ENABLE );
}
   
void OPA_IRQHandler(void) __attribute__((interrupt("WCH-Interrupt-fast")));

/*********************************************************************
 * @fn      OPA_IRQHandler
 *
 * @brief   This function handles OPA exception.
 *
 * @return  none
 */
void OPA_IRQHandler(void)
{
          
    if(OPA_GetFlagStatus(OPA_FLAG_OUT_CNT)!=RESET)
    {

    IntResponse = 1 ;
    OPA_ClearFlag(OPA_FLAG_OUT_CNT);     /* Clear Flag */
    }
   
}

/*********************************************************************
 * @fn      main
 *
 * @brief   Main program.
 *
 * @return  none
 */
int main(void)
{
    NVIC_PriorityGroupConfig(NVIC_PriorityGroup_1);
    SystemCoreClockUpdate();
    Delay_Init();
    USART_Printf_Init(115200);
    printf("SystemClk:%d\r\n", SystemCoreClock);
    printf( "ChipID:%08x\r\n", DBGMCU_GetCHIPID() );
    OPA_Unlock();
    OPA_POLL_Unlock();
    OPA2_Init();

    while(1)
    {
        if(IntResponse == 1)
        {
			IntResponse=0;
            printf("POLL END\r\n");
        }
        
    }
}

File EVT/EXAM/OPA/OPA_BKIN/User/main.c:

/********************************** (C) COPYRIGHT *******************************
 * File Name          : main.c
 * Author             : WCH
 * Version            : V1.0.3
 * Date               : 2026/10/16
 * Description        : Main program body.
 *********************************************************************************
 * Copyright (c) 2021 Nanjing Qinheng Microelectronics Co., Ltd.
 * Attention: This software (modified or not) and binary are used for 
 * microcontroller manufactured by Nanjing Qinheng Microelectronics.
 *******************************************************************************/

/*
 *@Note
 *OPA output braking routines:
 *OPA2_CHP0--PA7
 *OPA2_CHN1--PA5
 *OPA2_OUT--PA4
 *When the output signal is high level, TIM2 brake is effective.PB9--CH1  PB6--C1N
 */

#include "debug.h"

/*********************************************************************
 * @fn      OPA2_Init
 *
 * @brief   Initializes OPA2.
 *
 * @return  none
 */
void OPA2_Init( void )
{
    GPIO_InitTypeDef GPIO_InitStructure = {0};
    OPA_InitTypeDef  OPA_InitStructure = {0};

    RCC_APB2PeriphClockCmd( RCC_APB2Periph_GPIOA, ENABLE );
    GPIO_InitStructure.GPIO_Pin = GPIO_Pin_7|GPIO_Pin_5;
    GPIO_InitStructure.GPIO_Mode = GPIO_Mode_AIN;
    GPIO_Init( GPIOA, &GPIO_InitStructure );

    GPIO_InitStructure.GPIO_Pin = GPIO_Pin_4;
    GPIO_InitStructure.GPIO_Mode = GPIO_Mode_IN_FLOATING;
    GPIO_Init( GPIOA, &GPIO_InitStructure );

    OPA_InitStructure.OPA_NUM=OPA2;
    OPA_InitStructure.PSEL = CHP0;
    OPA_InitStructure.NSEL = CHN0;
    OPA_InitStructure.Mode=OUT_IO_OUT0;
    OPA_InitStructure.PSEL_POLL=CHP_OPA1_ON_OPA2_ON;
    OPA_InitStructure.OPA_POLL_Interval=0x50;
    OPA_InitStructure.BKIN_EN=BKIN_OPA1_ON_OPA2_ON;
    OPA_InitStructure.BKIN_SEL=BKIN_OPA1_TIM2_OPA2_TIM1;
    OPA_Init( &OPA_InitStructure );
    OPA_Cmd(OPA2, ENABLE );
}

/*********************************************************************
 * @fn      TIM1_PWM_In
 *
 * @brief   Initializes TIM1 input capture.
 *
 * @param   arr - the period value.
 *          psc - the prescaler value.
 *          ccp - the pulse value.
 *
 * @return  none
 */
void TIM1_PWM_In( u16 arr, u16 psc, u16 ccp )
{
    GPIO_InitTypeDef GPIO_InitStructure = {0};
    TIM_OCInitTypeDef TIM_OCInitStructure = {0};
    TIM_TimeBaseInitTypeDef TIM_TimeBaseInitStructure = {0};
    TIM_BDTRInitTypeDef TIM_BDTRInitStructure = {0};
  
    RCC_APB2PeriphClockCmd( RCC_APB2Periph_GPIOA  | RCC_APB2Periph_GPIOB | RCC_APB2Periph_TIM1 , ENABLE );

    GPIO_InitStructure.GPIO_Pin = GPIO_Pin_9|GPIO_Pin_6;
    GPIO_InitStructure.GPIO_Mode = GPIO_Mode_AF_PP;
    GPIO_InitStructure.GPIO_Speed = GPIO_Speed_50MHz;
    GPIO_Init( GPIOB, &GPIO_InitStructure );

    TIM_TimeBaseInitStructure.TIM_Period = arr;
    TIM_TimeBaseInitStructure.TIM_Prescaler = psc;
    TIM_TimeBaseInitStructure.TIM_ClockDivision = TIM_CKD_DIV1;
    TIM_TimeBaseInitStructure.TIM_CounterMode = TIM_CounterMode_Up;
    TIM_TimeBaseInit( TIM1, &TIM_TimeBaseInitStructure);
    TIM_OCInitStructure.TIM_OCMode = TIM_OCMode_PWM2;
    TIM_OCInitStructure.TIM_OutputState = TIM_OutputState_Enable;
    TIM_OCInitStructure.TIM_OutputNState = TIM_OutputNState_Enable;
    TIM_OCInitStructure.TIM_Pulse = ccp;
    TIM_OCInitStructure.TIM_OCPolarity = TIM_OCPolarity_High;
    TIM_OCInitStructure.TIM_OCNPolarity = TIM_OCNPolarity_Low;
    TIM_OCInitStructure.TIM_OCIdleState = TIM_OCIdleState_Set;
    TIM_OCInitStructure.TIM_OCNIdleState = TIM_OCNIdleState_Set;
    TIM_OC1Init( TIM1, &TIM_OCInitStructure );

    TIM_BDTRInitStructure.TIM_OSSIState = TIM_OSSIState_Enable;
    TIM_BDTRInitStructure.TIM_OSSRState = TIM_OSSRState_Enable;
    TIM_BDTRInitStructure.TIM_LOCKLevel = TIM_LOCKLevel_OFF;
    TIM_BDTRInitStructure.TIM_DeadTime = 0x01;
    TIM_BDTRInitStructure.TIM_Break = TIM_Break_Enable;
    TIM_BDTRInitStructure.TIM_BreakPolarity = TIM_BreakPolarity_High;
    TIM_BDTRInitStructure.TIM_AutomaticOutput = TIM_AutomaticOutput_Disable;
    TIM_BDTRConfig( TIM1, &TIM_BDTRInitStructure );

    TIM_CtrlPWMOutputs(TIM1, ENABLE );
    TIM_OC1PreloadConfig( TIM1, TIM_OCPreload_Disable );
    TIM_ARRPreloadConfig( TIM1, ENABLE );
    TIM_Cmd( TIM1, ENABLE );
}

/*********************************************************************
 * @fn      main
 *
 * @brief   Main program.
 *
 * @return  none
 */
int main(void)
{
    NVIC_PriorityGroupConfig(NVIC_PriorityGroup_1);
    SystemCoreClockUpdate();
    Delay_Init();
    USART_Printf_Init(115200);
    printf("SystemClk:%d\r\n", SystemCoreClock);
    printf( "ChipID:%08x\r\n", DBGMCU_GetCHIPID() );
    OPA_POLL_Unlock();
    OPA_Unlock();
    OPA2_Init();
    TIM1_PWM_In( 100-1, 4800-1, 500 );

    while(1);
}

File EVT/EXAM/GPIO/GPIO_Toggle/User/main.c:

/********************************** (C) COPYRIGHT *******************************
 * File Name          : main.c
 * Author             : WCH
 * Version            : V1.0.0
 * Date               : 2023/12/26
 * Description        : Main program body.
*********************************************************************************
* Copyright (c) 2021 Nanjing Qinheng Microelectronics Co., Ltd.
* Attention: This software (modified or not) and binary are used for
* microcontroller manufactured by Nanjing Qinheng Microelectronics.
*******************************************************************************/

/*
 *@Note
 *GPIO routine:
 *PA0 push-pull output.
 *
 ***Only PA0--PA15 and PC16--PC17 support input pull-down.
 */

#include "debug.h"

/* Global define */

/* Global Variable */

/*********************************************************************
 * @fn      GPIO_Toggle_INIT
 *
 * @brief   Initializes GPIOA.0
 *
 * @return  none
 */
void GPIO_Toggle_INIT(void)
{
    GPIO_InitTypeDef GPIO_InitStructure = {0};

    RCC_APB2PeriphClockCmd(RCC_APB2Periph_GPIOA, ENABLE);
    GPIO_InitStructure.GPIO_Pin = GPIO_Pin_0;
    GPIO_InitStructure.GPIO_Mode = GPIO_Mode_Out_PP;
    GPIO_InitStructure.GPIO_Speed = GPIO_Speed_50MHz;
    GPIO_Init(GPIOA, &GPIO_InitStructure);
}

/*********************************************************************
 * @fn      main
 *
 * @brief   Main program.
 *
 * @return  none
 */
int main(void)
{
    u8 i = 0;

    NVIC_PriorityGroupConfig(NVIC_PriorityGroup_1);
    SystemCoreClockUpdate();
    Delay_Init();
    USART_Printf_Init(115200);
    printf("SystemClk:%d\r\n", SystemCoreClock);
    printf( "ChipID:%08x\r\n", DBGMCU_GetCHIPID() );
    printf("GPIO Toggle TEST\r\n");
    GPIO_Toggle_INIT();

    while(1)
    {
        Delay_Ms(500);
        GPIO_WriteBit(GPIOA, GPIO_Pin_0, (i == 0) ? (i = Bit_SET) : (i = Bit_RESET));
    }
}

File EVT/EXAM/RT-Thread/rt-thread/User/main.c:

/********************************** (C) COPYRIGHT *******************************
 * File Name          : main.c
 * Author             : WCH
 * Version            : V1.0.0
 * Date               : 2024/03/02
 * Description        : Main program body.
*********************************************************************************
* Copyright (c) 2021 Nanjing Qinheng Microelectronics Co., Ltd.
* Attention: This software (modified or not) and binary are used for 
* microcontroller manufactured by Nanjing Qinheng Microelectronics.
*******************************************************************************/
#include "ch32x035.h"
#include <rtthread.h>
#include <rthw.h>
#include "drivers/pin.h"
#include "ch32x035_conf.h"

/* The printf pin is PA2 (UART2) */


/* Global typedef */

/* Global define */

/* LED0 is driven by the pin driver interface of rt  */
#define LED0_PIN  5   //PA0

/* Global Variable */
/*CH32X035F8 PB1 and PB5 are the same physical pin
 *  PB1 and PB5 cannot be used at the same time. */
#define  PB1  0
#define  PB5  1
#define  PB1_5  PB1

/*********************************************************************
 * @fn      LED1_BLINK_INIT
 *
 * @brief   LED1 directly calls the underlying driver
 *
 * @return  none
 */
void LED1_BLINK_INIT(void)
{
    GPIO_InitTypeDef GPIO_InitStructure={0};
    RCC_APB2PeriphClockCmd(RCC_APB2Periph_GPIOA, ENABLE);
    GPIO_InitStructure.GPIO_Pin = GPIO_Pin_0;
    GPIO_InitStructure.GPIO_Speed = GPIO_Speed_50MHz;
    GPIO_InitStructure.GPIO_Mode = GPIO_Mode_Out_PP;
    GPIO_Init(GPIOA, &GPIO_InitStructure);
}
/* main is just one of the threads, in addition to tshell,idle
   *    main is just an LED blinking, the main thread is registered in rtthread_startup,
   *   tshell uses the serial port to receive interrupts, and the interrupt stack and thread stack are
   *   used separately.Note that when entering an interrupt, the 16caller register needs to be pushed 
   *   into the thread stack
 * */

int main(void)
{

    rt_kprintf("\r\n MCU: ch32x035\r\n");
	rt_kprintf(" SysClk: %dHz\r\n",SystemCoreClock);
    rt_kprintf(" www.wch.cn\r\n");
	LED1_BLINK_INIT();
	GPIO_ResetBits(GPIOA,GPIO_Pin_0);
	while(1)
	{
	    GPIO_SetBits(GPIOA,GPIO_Pin_0);
	    rt_thread_mdelay(500);
	    GPIO_ResetBits(GPIOA,GPIO_Pin_0);
	    rt_thread_mdelay(500);
	}
}

/* Test using the driver interface to operate the I/O port  */
int led(void)
{
    rt_uint8_t count;

    rt_pin_mode(LED0_PIN, PIN_MODE_OUTPUT);
    printf("led_SP:%08x\r\n",__get_SP());
    for(count = 0 ; count < 10 ;count++)
    {
        rt_pin_write(LED0_PIN, PIN_LOW);
        rt_kprintf("led on, count : %d\r\n", count);
        rt_thread_mdelay(500);

        rt_pin_write(LED0_PIN, PIN_HIGH);
        rt_kprintf("led off\r\n");
        rt_thread_mdelay(500);
    }
    return 0;
}
MSH_CMD_EXPORT(led,  led sample by using I/O drivers);

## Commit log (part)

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2026-06-15 update update script and add GitHub Actions workflow for automated datasheet downloads
2026-06-15 update cron schedule in GitHub Actions workflow and enhance download script with retry logic
2026-06-15 refactor update job to simplify commit logic in GitHub Actions workflow
2026-06-16 update GitHub Actions schedule
2026-06-19 update GitHub Actions workflow to implement keepalive logic and remove unnecessary permissions
2026-06-19 refactor fetch function in update.sh to simplify error handling and remove retry logic
2026-06-25 update (automated)
